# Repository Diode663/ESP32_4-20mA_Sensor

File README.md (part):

# ESP32 4-20mA ESPHome Sensor Board

Single-channel industrial 4-20mA current-loop reader, USB-C powered, built for ESPHome.

## Rev H (2026-11-11)

Rev G was never ordered; its files, fab package included, are at tag `rev-g`.
Rev H carries the changes that came out of an independent review of it
(`docs/Design_Review_2026-11-11_independent.md`). The sections further down
still describe Rev G except where they say Rev H.

| Change | Why |
|---|---|
| **mA input: D5 SMAJ12A -> SMAJ28A, new F1 (100 mA / 60 V PPTC) in series, new D6 (1N4007W) across the shunt.** Nets: `LOOP_IN` terminal side, `LOOP_RTN` shunt side | D5 did not conduct until 13 V with the 3.32 ohm shunt in parallel: a 0.5 kV surge put 5 A / 91 W peak through an 0805, and 24 V wired to the mA pin put 7 A through it. Now the shunt sees D6's ~1 V and F1 opens (`sim/8_input_protection.py`). Cost: D6 steals 1 ppm of the reading at 25 C, 77 ppm at 85 C |
| **R15 is a pull-down** | the loop supply stays off through reset, flashing and a hung firmware; ESPHome turns it on at boot. The same firmware runs on Rev G |
| **Silkscreen legend**: J2 pinout (top, and on the bottom under each pin), RESET, BOOT, board name and revision | Rev G carried designators only |
| **Routing by this board's own grid router** (`gridroute.py`), module supply scripted through C3 | 9 signal vias and 25 mm of track on the ground layer; Rev G's Freerouting result had 7 vias and 59 mm, with pin 2 fed through two vias |
| **Terminal corner re-laid**: F1 where D3 was, D6 beside it, D3 upright at the row's east end, D4 in the strip right of the terminal, TP1 beside R20, third fiducial moved to the west edge | to fit two more parts; nothing live is within 2.6 mm of the corner mounting hole's centre |
| **Schematic redrawn on A3**: every block wired (no connection made by label inside a block), functional symbols for J1, D1, U3, U4, U5 | Rev G's A2 sheet printed at half size and joined 20 connections by name |

DRC: the same nine library-footprint items as Rev G, nothing unconnected,
schematic parity clean. Not built or measured.

## Rev G at a glance (2026-09-20)

Rev G is the result of a second, independent design review
(`docs/Design_Review_2026-09-20_second_pass.md`). Every circuit change below
was simulated first; the decks are in `sim/` and run on KiCad's own bundled
ngspice.

| Change | Why |
|---|---|
| Limiter is now **constant-current**: R19 removed, R16 18 ohm, Q1 -> BCP53-16 (SOT-223) | Rev F's foldback could park a transmitter at ~9 V / 14 mA after a short or a hot-plug and report that as the reading |
| **D4** (1N4148W) in series after Q1 | a surge on `LOOP_V` drove Q1 backwards into the 24 V rail from ~25 V, long before the TVS conducted |
| **D3 -> SMAJ28A to GND**, new **D5** SMAJ12A from `LOOP_RTN` to GND | one TVS across the pair handled only differential surges; common-mode went through the shunt into the INA226 |
| **Soft-start load switch** Q3/Q4/R21/R22/C12 ahead of the boost | VBUS saw ~27 uF at attach against USB's 10 uF limit; it now sees 1 uF, and `MT_EN` low truly disconnects the loop supply |
| **J2 is 3-pin**: GND, mA in, +24 V out | a 3-wire or self-powered (sourcing) transmitter could not be connected at all |
| **J2 is a one-piece push-in block**, KEFA KF250NH-5.0-3P (`C976567`) | no separate plug to order or lose; solid and ferruled wire pushes straight in, the orange button releases it or opens it for bare stranded wire |
| **U1 is the ESP32-S3-WROOM-1U-N4** (`C2980296`): U.FL connector, external antenna | antenna goes on the enclosure, not inside it. **The board is unchanged** - see below |
| L1 4.7 -> **22 uH** | a quarter of the ripple current at this light load |
| Boost and INA226 re-placed to their **datasheet layout figures** | switched-current loop 28 -> 19 mm^2 with C11's ground 3.8 mm from U5's (was 9.7); C8 1.5 mm from VS (was 8.0, on the wrong side of the chip) |
| Top M2 holes moved from the corners to y = 16.8 mm | they were level with the antenna, 9.6 mm from the module |
| `pcblib`: swaps changed footprints, DRC runs with `--schematic-parity` | the board had kept 1.5 mm test pads the schematic dropped for 1.0 mm, and nothing could see it |

**State:** 28 nets / 35 no-connects match the specification exactly, ERC 0
errors, schematic parity clean, placement DRC 4 (all deliberate silk-at-edge)
+ 5 library-internal, 52 parts + 4 holes + 3 fiducials, BOM 34 lines / 47
placements. **Placed and routed** - 0 unconnected, DRC unchanged at 4 + 5; see
[Routing](#routing).

**Firmware:** `firmware/` holds the ESPHome configuration, and both of the
things this board's firmware had to do are done there:

1. A reading is published as *unknown*, not as a plausible number, whenever
   the loop is not trustworthy - including `LOOP_V` below 20 V with current
   flowing. On a sustained short (`LOOP_V` < 3 V) it drops `MT_EN`, which now
   removes the supply entirely, retries three times and then latches off.
2. Two-point calibration at 4 mA and 20 mA, captured from Home Assistant with
   a reference source and stored in flash. R12's 1 % tolerance and 200 ppm/°C
   drift and R20's fixed gain error all come out together; one point cannot
   remove them.

The firmware is a reusable ESPHome package, pulled by URL, so another board
built from this design tracks the same definition.

It also classifies faults to NAMUR NE43 and detects a backwards-wired sourcing
transmitter, which reads as negative current through the shunt. Validated on
ESPHome 2026.9.0: config clean, and it compiles to 47 % of the N4's
application partition. See `firmware/README.md`.

### Going back to the PCB-antenna module

The -1U was swapped in **without touching the board**, deliberately. Espressif's
datasheet gives the -1 and the -1U one land pattern (Figures 10 and 11 carry
identical dimensions; the -1 only adds the antenna area), so the new footprint
`WIFIM-SMD_ESP32-S3-WROOM-1U` copies the old one's 61 pads and its origin
unchanged and differs only in body outline and 3D model. The outline, the
6.5 mm the antenna would overhang, the keep-clear at the top edge and the
lowered top mounting holes are all still laid out for the -1.

To revert, change one line in `generate_schematic.py` (the old line is kept
there as a comment) and re-run both generators. No copper moves.

With the -1U fitted the radio has **no antenna of its own**: the U.FL pigtail
and antenna in `bom/non-bom-items.csv` are required, and the connector is
U.FL / IPEX generation 1 - the smaller Gen 3/4 (MHF3/MHF4) plugs do not mate.

## Calibration

**Do this before you trust a reading.** R12 is a 1 % shunt with 200 ppm/°C
drift, and R20 adds a fixed 1.19 % gain error to the voltage reading. A single
point cannot remove both a gain and an offset error, which is why there are
two. The firmware ships with the identity calibration, so an uncalibrated
board is out by whatever its own components happen to be.

You need a loop calibrator, or any adjustable current source you trust to
better than the accuracy you want out of the board.

1. Wire the calibrator into **J2 pins 3 and 2** as if it were a 2-wire
   transmitter — the board supplies the 24 V and the calibrator sinks the
   current. An active source works too: push into pin 2, return on pin 1, and
   turn *Loop power* off first so the two supplies do not fight.
2. Set **4.000 mA**. Watch the `Loop current (raw)` entity and wait for it to
   settle — the median filter takes about 3 s, so give it ten.
3. Press **Calibrate: capture 4 mA**.
4. Set **20.000 mA**, wait again, press **Calibrate: capture 20 mA**.
5. Read the **Calibration** entity. It reports the pair you captured together
   with the resulting gain and offset, for example
   `4mA=4.0123  20mA=19.9871  gain=1.00212  offset=-0.0208 mA`.
   A gain more than a couple of percent from 1.000 means something is wrong —
   check the shunt and the wiring rather than accepting it.

A capture is **refused** if the raw reading is more than 2 mA away from the
reference it claims to be, and the log says so. That is deliberate: it stops a
mistimed press silently destroying the calibration.

The result is written to flash and survives reboots and OTA updates.
**Calibrate: reset to factory** puts back the values compiled into the YAML.

Recalibrate if the board's ambient temperature changes substantially: the
shunt's 200 ppm/°C over a 40 °C swing is 0.8 % of reading, about 0.13 mA
across the span. Full procedure and the entity list are in
[`firmware/README.md`](firmware/README.md).

## Project files

```
esp32-4to20ma-board.kicad_pro     Project file
esp32-4to20ma-board.kicad_sch     The schematic — one A3 sheet in Rev H, A2 in Rev G (generated)
schematic.pdf                     PDF of the schematic
esp32-4to20ma-board.kicad_pcb     Board, 40x61mm portrait — placed and routed
setup_fab.py                      Stackup, netclasses, board rules, .kicad_dru (run before routing)
route_board.py                    Routes the board: scripted critical nets + replayed autoroute + pours
routelib.py                       Routing library (from the kicad-pcb-placement skill): drawing, the
                                  Freerouting hand-off, replay, DRC and pour reports
routing/autoroute.json            Freerouting's result (Rev G), replayed with --freerouting
gridroute.py                      Rev H: this board's own grid router (route_board.py --gridroute)
routing/gridroute.json            Its result, replayed by route_board.py by default
routing/drc.json                  The last full DRC report
build_package.py                  Builds fab/: gerbers zip, BOM, CPL, order notes (DRC-gated)
jlc_cpl.py, jlc_rotations.json    CPL exporter and this board's sourced rotation corrections
jlc_compare.py                    Derives those corrections from JLCPCB's own footprints
fab/                              The JLCPCB upload, regenerated by build_package.py
place_components.py               Places every part; the source of truth for the layout
pcblib.py                         PCB builder (from the kicad-pcb-placement skill)
.pcbgen-backup/                   Backups of the board and of the original footprints
sym-lib-table / fp-lib-table      Project-local + KiCad-standard library references
libraries/                        Project-local symbols, footprints, 3D models from LCSC
datasheets/manifest.json          Which manufacturer datasheet was read for each
                                  IC, and where to get it — the PDFs themselves
                                  are copyrighted and not in this repository
firmware/                         ESPHome configuration — a shared package plus
                                  a thin per-device file. See firmware/README.md
bom/bom.csv                       BOM with LCSC part numbers, for JLCPCB turnkey
bom/non-bom-items.csv             Parts to order that aren't on the board
bom_report.py                     Regenerates bom/bom.csv from the schematic
docs/Design_Review_2026-09-20.md  Design review (schematic + placement, pre-fab)
docs/Design_Review_2026-09-20_second_pass.md   Second, independent review - what Rev G fixes
sim/                              ngspice decks for the limiter, surge path and USB inrush
analysis/                         Analyzer JSON per run, tracked by manifest.json
generate_schematic.py             Generates the schematic — the source of truth
schlib.py                         Schematic builder (from the kicad-schematic-layout skill)
.schgen-backup/                   Automatic backups of any sheet the generator overwrote
verify_schematic.py               Diffs KiCad's extracted netlist against the spec
netlist_report.py                 Regenerates netlist_report.txt
netlist_report.txt                Pin-level connectivity listing for rework
erc_report.txt                    Verification output (0 errors)
render/pcb_top.png                3D top view, written by place_components.py
render/pcb_angled.png             3D angled view
render/pcb_bottom.png             3D bottom view
render/copper_top.svg, copper_bottom.svg   The copper layers as drawn
render/pcb.svg                    Vector top view
render/pcb_top_pad_overlay.png    The top view with the real pad rectangles drawn
                                  over it — how the J2 pitch error and the three
                                  misplaced 3D models were caught
```

## Schematic organisation

The schematic is **one A2 sheet**. At 47 parts plus five test points the design still isn't complex
enough to justify hierarchy, which would only add page-flipping. The sheet has
four sections, tiled in signal-flow order:

```
USB-C INPUT & ESD   ->   3.3 V REGULATOR & LED   ->   ESP32-S3 MODULE
24 V BOOST CONVERTER   ->   LOOP CURRENT LIMITER   ->   LOOP TERMINAL & MEASUREMENT
TEST POINTS, sheet notes
```

One block per **circuit**, seven in all (it was twelve). The boost converter is
one block with its load switch, input and output in it, not three; the module is
one block with its reset, boot, pull-ups, decoupling and strapping notes, not
"module" and "support circuitry". Reference sheets for these parts are drawn the
same way - Adafruit's ESP32-S3 Feather divides its sheet into "POWER AND
FILTERING", "USB TO SERIAL CONVERTER", "LIPO CHARGING" and so on, with the module
and everything that serves it in one region.

Drawing conventions throughout:

- **Flow and orientation:** signals flow left to right; supplies come in from
  the top and grounds leave at the bottom.
- **Power rails:** `GND`, `+3V3`, `+5V` and `+24V` are drawn as power-port
  symbols, not text labels.
- **Links between sections:** the sections connect by net label — `USB_P` and
  `USB_N` from USB-C to the ESP32-S3, and `I2C_SDA` and `I2C_SCL` from the
  ESP32-S3 to the INA226.
- **Wires vs labels:** components are wired with real wires and junctions.
  Short labelled stubs are used only where a wire would cross another net: the
  USB-C flip pairing, the CC pulldowns, the MT3608's FB/SW pins and the INA226
  sense lines. There are no wire crossings on the sheet.
- **Blocks and notes:** each circuit is drawn inside `s.block_start(title)` /
  `s.block_end()`, with its design calculations as notes *inside* the block.
  No rectangle is typed by hand: `schlib` derives each outline from what is in
  the block (parts, field text, labels, notes, measured at KiCad's own glyph
  widths) plus 5 mm, and `arrange()` flows the blocks across the page in the
  order they are declared. `check_text()` then reads KiCad's render and fails
  on any string or part body within 0.8 mm of an outline. Run against the old
  hand-boxed sheet that check reports about a hundred such faults (`I2C_SCL`
  on the module box's edge, the strapping notes across another, `+24V` on the
  limiter's top line); on this sheet, none.

### Regenerating

`generate_schematic.py` is the source of truth. Edit it rather than the
`.kicad_sch` file, which gets regenerated:

```bash
python3 generate_schematic.py && python3 netlist_report.py
```

The generator re-checks the geometry and verifies the drawn netlist against its
`NETS` spec, using KiCad's own netlister. It also runs ERC, then a text check.
The text check reads KiCad's rendered SVG and flags any reference, value,
label or note that is drawn sideways, lies on a wire, or overlaps a part.

If the sheet was changed in KiCad since the last run, the generator refuses to
overwrite it. It backs the file up to `.schgen-backup/` first; port your edits
into the script, then rerun with `--force`.

### PCB after the switch to one sheet

Footprints are linked to schematic symbols by the symbols' sheet path, and
flattening the hierarchy changed every path. Update the PCB like this:

1. Run **Tools → Update PCB from Schematic**.
2. Tick **"Re-link footprints to schematic symbols based on their reference
   designators"**. All references are unchanged, so every footprint re-links.
3. Expect local net names to change prefix, e.g. `/USB-C Input…/CC1` → `/CC1`.
   The board has almost no routing yet, so nothing is lost.

From now on, UUIDs are deterministic, so regenerating won't break the links
again.

## Routing

The board is **routed**: 0 unconnected items, DRC at the same 4 + 5 it had as a
bare placement (four deliberate silk-at-edge warnings, five inside library
footprints), schematic parity clean. Two scripts, run in this order after
`place_components.py`:

```bash
"C:\Program Files\KiCad\10.0\bin\python.exe" setup_fab.py
"C:\Program Files\KiCad\10.0\bin\python.exe" route_board.py
```

`setup_fab.py` writes the JLCPCB 2-layer stackup (JLC0216A, 1.6 mm), the
netclasses (`USB` 0.25/0.20 mm pair, `POWER` 0.4 mm, `LOOP` 0.3 mm with 0.25 mm
clearance, `GND`) and a three-rule `.kicad_dru`. The board constraints are the
ones in *Fabrication rules* below, unchanged.

`route_board.py` is a **hybrid**. It removes every track, via and copper zone
and redraws them, so it is safe to run again after any placement change - and
it **discards hand edits to tracks**; change the script, or stop using it.

| Scripted (255 segments and vias) | Why it is not left to an autorouter |
|---|---|
| MT3608 boost | Figure 3: CIN returns to pin 2 *under* the IC, COUT returns down the east side of D2, the switch node is two stubs under 2 mm, FB is 1 mm from pin 3 to the divider |
| INA226 taps | Figure 30: the two taps enter the shunt pads on their inner faces as a pair; load current enters and leaves on the outer faces. R14.1 is on GND by name only, so the pour is kept off it - it sees the shunt pad and nothing else |
| USB-C fan-out, D1, the pair | see below |
| +5V, +3V3 and +24V trunks, the 24 V loop | widths, and the one place each may change layer |
| Q1's copper | tab and pin 2 are one area top and bottom (40 + 45 mm2), six vias under the body |
| every ground via, both pours | the bottom pour is **one unbroken piece** of 2179 mm2 |

Freerouting 2.4.1 does the rest - EN, IO0, MT_EN, I2C, the load-switch gate
network, the LED and the +3V3 branches: 113 segments, 7 vias. It runs only with
`route_board.py --autoroute`; its result is stored in `routing/autoroute.json`
and replayed on every ordinary run, so the board is reproducible (two runs give
byte-identical tracks) without Java and without re-rolling the autorouter. Run
`--autoroute` again if a part that only it touches moves. Runs differ: each one is
judged by KiCad's own DRC on a trial board and repeated (up to three times) until
nothing is left open, and `FREEROUTING_BEST_OF=3` keeps the best of three. Look at
the result either way - one re-roll here passed DRC with the bottom ground in two
pieces. It expects
`~/tools/freerouting/` (or `FREEROUTING_HOME`) to hold `freerouting-2.4.1.jar` and a Java
25 runtime; it runs headless, with the fan-out stage and telemetry off.

Three things about KiCad 10 + Freerouting 2.4.1 that cost time and are handled
in `routelib.py`: KiCad exports existing tracks as `(type route)`, which an
autorouter may rip up, so the DSN is patched to `(type protect)`; KiCad's
`ImportSpecctraSES` then refuses the session file, so the script reads the SES
itself and takes only unprotected items on nets it did not route; and
Freerouting does not count a track that ends inside a pad, off its centre, as
connected, so whatever it adds to a fully scripted net is dropped as a duplicate.

**USB.** J1's D+/D- pads read N P N P. The *outer* two (B7, B6) are the main
path - D- west, D+ east - which is the order both D1 (turned 180 degrees) and
module pins 13/14 want, so the pair never crosses itself. A6 joins D+ on the top
layer; A7 joins D- by the only bottom strap in the pair, 2.9 mm. The two VBUS
pins are joined on the board by a 4.8 mm bottom link under D1, which also feeds
D1's pin 5 (a receptacle's VBUS pins are only joined inside a plug). The pair
is 39.6 / 43.8 mm including those stubs; at the S3's 12 Mbit/s full speed the
4 mm difference is about 25 ps against an 83 ns bit.

**Where the bottom ground is cut**, all of it: the two USB-entry links above,
one SDA hop of 9.8 mm that passes under the pair at 45 degrees, +3V3 to the
pull-ups and U3 (39 mm in two runs, about 1 mA), and LOOP_V's sense tap to R20
(10.5 mm). Nothing crosses under the boost converter.

**Placement changes routing asked for** (all in `place_components.py`): D1
turned 180 degrees and moved up 1.5 mm; R7 and R8 moved into the lanes between
VBUS and the pair, 2 mm from their pins; R10/R11 moved beside U5, which lets
+24V reach the limiter on the top layer; C9 up 0.1 mm; R6 and R15 swapped so
each pull-up sits under its own pin (before that, MT_EN took a 25 mm detour
under the module).

Still open after routing: nothing has been measured. EMC and Q1's temperature
are as designed, not as tested.

## Fabrication package (JLCPCB)

```bash
"C:\Program Files\KiCad\10.0\bin\python.exe" build_package.py
```

writes `fab/`: `esp32-4to20ma-board_gerbers.zip` (9 layers + separate PTH and NPTH drill
files + drill maps), `_bom.csv` (34 lines, 47 parts), `_cpl.csv` (47 placements) and
`ORDER_NOTES.txt`. It refuses to build unless DRC is clean apart from the two accepted
errors inside J1's library footprint, the BOM is read from the board so it is exactly
what is placed, and the build stops if BOM and CPL designators differ or the board
disagrees with `bom/bom.csv`.

Three things to know before ordering:

- **Standard PCBA, not Economic.** JLCPCB lists the ESP32-S3-WROOM-1U-N4 (`C2980296`)
  as "PCBA Type: Standard Only". J2 is the one through-hole part; it is "Economic and
  Standard", wave-soldered, and rides along.
- **Rotations were derived, not guessed.** `jlc_compare.py` fetches JLCPCB's own
  footprint for each part's LCSC number and matches it to the board's, pad number to
  pad number. Every project-library footprint is already at JLCPCB's zero with zero
  origin offset. Only the four stock-KiCad transistor footprints differ - Q1 (SOT-223)
  and Q2, Q3, Q4 (SOT-23) need +180 - and those are in `jlc_rotations.json`, each with
  its evidence. None of it has been seen in JLCPCB's placement preview yet:
  `ORDER_NOTES.txt` says what each part should look like there. LED1's polarity rests on
  pad 1 being the cathode in their footprint (its silk says so; their symbol could not
  be fetched to confirm) - a reversed LED only stays dark.
- **All 34 lines were in stock at LCSC on 2026-09-20**, thinnest: U1 1,702, J2 1,990,
  R12 4,810, C10/C11 8,605. Nine manufacturer names in the BOM were wrong (the Samsung
  capacitors were listed as CCTC, the FOJAN resistors as Uniroyal, LED1 as
  "Nichia-compatible" - it is Nationstar) and were corrected in `generate_schematic.py`;
  every MPN and LCSC number was already right.

## PCB placement

Components are placed on a **40 × 61 mm** two-layer board,
portrait, with 1 mm rounded corners, by `place_components.py` on top of
`pcblib.py`. Run it with KiCad's Python:

```bash
"C:\Program Files\KiCad\10.0\bin\python.exe" place_components.py
```

**Re-running resets every part to the table.** Once you start adjusting
placement by hand, editing the `PLACEMENT` table is the only safe way to
change it. `pcblib` enforces this: it hashes the board each time it writes,
and if the file has changed since, it backs it up to `.pcbgen-backup/` and
refuses. Port your changes into the table, then run with `--force`.

Each run also:

- imports any footprint the schematic has and the board lacks, and reloads
  every footprint from its library, so schematic and `.kicad_mod` changes
  both reach the board without a trip through the KiCad GUI;
- re-links every footprint to its schematic symbol by UUID and assigns pad
  nets from KiCad's own netlist, so the ratsnest is right immediately and
  *Update PCB from Schematic* finds nothing to change;
- puts each reference designator where it clears pads, silkscreen, its
  neighbours and the board edge, at 0.15 mm stroke (JLCPCB's minimum);
- checks courtyard overlaps, **pad-to-pad gaps between different parts**,
  off-board parts and keep-out intrusions before saving, and aborts rather
  than writing a broken board. The pad-gap check matters: 8 of these 52
  footprints draw their courtyard around the body and leave the pads
  outside it (SW1 by 2.66 mm), so courtyard clearance flatters them. It
  caught the buttons sitting 0.35 mm from the module's pad row and the CC
  resistors 0.21 mm from J1 — both legal for DRC, both far too tight;
- runs DRC and **splits it in two** — placement problems, which are yours to
  fix, and problems inside a single library footprint, which moving parts
  cannot fix. Expect **4** and **5** respectively, 0 unconnected items, and
  `schematic parity: clean`. (Run it after moving a part and it will report
  shorts until `route_board.py` has been run again - the old tracks are still
  where the part used to be);
- prints the span of the critical nets, so the claims below are measurable
  rather than asserted;
- writes `render/pcb_top.png`, `render/pcb_angled.png` and `render/pcb.svg`.

All 5 placement-level warnings are `silk_edge_clearance`, on J1 where the
USB-C shell meets the board edge and on U1 where the module crosses the top
edge to overhang it - both deliberate.

`tidy_references` orders parts by `_part_extent()` (pads, silkscreen and
courtyard, deliberately blind to the text) with a natural sort on the
reference as tie-break, so repeated runs give byte-identical designator
positions. In Rev G it also searches further: the same eight spots with the
text turned upright, then both again up to 2 mm out, and it treats other
parts' courtyards as obstacles - pads and silk alone left the middle of the
SOT-223 looking like free board, and it put R12's designator there.

That still cannot solve the lower-right corner, which holds the limiter, the
sense network, two TVS diodes and the terminal. `REF_PINS` in
`place_components.py` places 18 designators by hand, each checked against DRC.

Five test points (`TP1`-`TP5`, 1.0 mm bare pads) sit on `LOOP_V`, `LOOP_RTN`
(`LOOP_IN` in Rev H), `+24V`, `+3V3` and `MT_EN`. In Rev H TP1 is the bare pad
beside R20 and carries no designator: there is no room for one. They are real schematic symbols - that is the only
way they get a net - but carry `in_bom=False`. Until Rev G the *board* still
held 1.5 mm pads: `pcblib` never propagated a footprint changed in the
schematic. It does now, and `Board.drc()` runs with `--schematic-parity`.

Four M2 holes: the bottom pair 3.5 mm in from the corners beside the
connectors, the top pair at y = 16.8 mm beside the buttons - 19 mm from the
antenna (Espressif asks for ~15 mm clear of metal) and 1.8 mm clear of the
button pads for a 4.6 mm standoff.

Three fiducials (`FID1`/`FID2`/`FID3`, 1 mm copper in a 2 mm mask opening)
sit at (4, 7), (36, 7) and (36, 54) mm — an L, 4 mm in from the edges, which
clears JLCPCB's 3.85 mm minimum. They are board-only footprints: no schematic
symbol, excluded from the BOM and from the placement file, so they cannot
become orphan designators in a PCBA upload.

`pcblib.py` is the shared library from the `kicad-pcb-placement` skill; it is
copied in so the project stays self-contained.

### Why the board is this shape

**Portrait, 40 × 61 mm.** About the minimum for this part set. The
measured extents are 2.40 mm of margin left and right — set by the M2
mounting holes, not by any component — J1's shell flush with the bottom edge,
and C3 1.80 mm from the top. Width is pinned by the bottom edge: J2's
courtyard is 12 mm wide (it includes the mating plug), J1's is about 10, and
the two corner mounting holes take 6 mm between them. Height is pinned by the
vertical stack: module 19 mm, buttons 7, boost 14, sense chain 10, connectors
10. The extra 1 mm over the first attempt buys ~1 mm of clearance either side
of the buttons.

**The antenna overhangs the top edge.** The board stops level with the start
of the module's pad rows, so 6.5 mm of antenna hangs in free air —
Espressif's best case, and better than any keep-out on a populated board. The
module is then soldered on three edges with that 6.5 mm unsupported, so the
enclosure needs clearance around it and must not press on it. There is no
antenna keep-out zone any more: the overhang replaced it. At routing time,
keep the ground pour back from the top edge.

**Both connectors are on the bottom edge**, as asked. Note that J2 is a
*vertical* plug-in header — the mating plug drops in from above — so its
position at the edge is for cable dressing, not because it needs edge access.

| Area | What's there | Why |
|---|---|---|
| Top, antenna overhanging | ESP32-S3 module, centred | No PCB under the antenna at all |
| Upper left | C3 at pin 2 (3V3), R1/C1 at EN, C2 bulk, R5 at pin 12 | The module's 3V3, EN and SDA pins are all on the left flank; each part sits level with the pin it serves |
| Below the module | RESET and BOOT buttons, R6 and R15 in the gap between them | SCL (17) and the loop enable IO10 (18) come out of the module's bottom edge, right where their pull-ups sit |
| Left, middle | AP2112K LDO + C6/C7 | Between its 5 V source at the bottom and its 3.3 V loads above |
| Right, middle | MT3608 boost: C10, L1, U5, D2, C11 in one tight loop, FB divider by the FB pin | Per the MT3608 datasheet, and the furthest point on the board from the antenna |
| Right, lower | INA226, shunt R12, R13/R14 tapping its two ends, C9 | Kelvin sense per the INA226 datasheet; U3 faces the shunt with its inputs and the MCU with its I²C |
| Bottom left | USB-C, D1 ESD clamp directly above it, CC pulldowns either side, LED on the left edge | D+/D− run connector → clamp → module with nothing in the way |
| Bottom right | 4-20 mA terminal J2, TVS D3 just above it aligned with its pins | Field wiring lands at the edge and is clamped immediately |

Measured after placement:

| Net | Span | Comment |
|---|---|---|
| `/MT_SW` | 5.45 mm | the boost switching node — the one that matters |
| `/LOOP_RTN` | 9.68 mm | terminal to shunt |
| Kelvin taps | 1.69 mm | R13 and R14 each sit against the shunt pad they measure |
| `/USB_P` / `/USB_N` | 35–36 mm | the cost of portrait: connector at the bottom, module at the top. Fine for the S3's 12 Mbps full-speed USB, but route them as a pair over unbroken ground |
| `/I2C_SDA` / `/I2C_SCL` | 28–35 mm | 400 kHz, length is irrelevant |

### Loop short-circuit protection

A boost converter cannot disconnect its output: `Vin -> L1 -> D2 -> Vout` is a
DC path that conducts with U5 disabled. Shorting Loop+ to Loop- therefore fed
~1.35 A from the 5 V rail straight through the shunt, destroying R12 (about
6 W in an 0805) and browning out the board.

The fix is a series element, which costs only compliance voltage, never
accuracy, because the transmitter regulates the loop current:

| | |
|---|---|
| Q1 | PNP pass element, **BCP53-16 in SOT-223** (80 V, 1.5 W) |
| R16 | 18 ohm sense; Q2 steals Q1's base drive once the drop across it reaches a Vbe |
| R18 | 1 k in Q2's base - limits its base current, nothing more |
| R17 | 47 k base bias, ~0.5 mA; BCP53-16 hFE >= 100 turns that into 50 mA |
| D4 | 1N4148W in series after Q1: blocks `LOOP_V` from driving Q1 backwards |

`Ilim = Vbe(Q2) / R16`: **35 / 33 / 30 / 27 mA at -20 / 25 / 60 / 85 C**
(`sim/6_rev_g_limiter.py`), so a 24 mA over-range reads at any temperature.
R16 + Q1 + D4 cost 1.2 V: **22.8 V at J2 with 20 mA flowing**.

**It is deliberately not a foldback limiter, and Rev F's was a mistake.** A
2-wire transmitter is a constant-current load: it draws the same current at
any voltage above its lift-off, so its load line can cross a foldback curve
twice, and the lower crossing is stable. After a short was cleared, or a
transmitter was plugged into a live J2, Rev F could sit at ~9 V / 14 mA
indefinitely with the process at 20 mA - and report 14 mA
(`sim/recover.py`). Its short-circuit current was also the small difference of
two ~0.6 V terms and fell to zero by ~65 C. Cold power-up happened to work,
which is why it looked fine.

The price is dissipation: a dead short puts the whole rail across Q1,
24 V x 35 mA = **0.85 W**. That is what the SOT-223 is for - pour `LOOP_C`
generously around the tab and stitch it to the bottom layer. Firmware should
also drop `MT_EN` on a sustained short; with the Rev G load switch that
removes the supply entirely rather than leaving 4.6 V behind.

### Field protection

**Rev H** keeps D3 and replaces the mA wire's single clamp with three parts:
D5 (now SMAJ28A, so 24 V on that pin is inside its stand-off) at the terminal,
F1 (100 mA hold, 60 V PPTC) in series, and D6 (1N4007W) across the shunt. A
surge or a mis-wired 24 V supply then puts D6's forward drop across the shunt
- 0.3 to 1 W peak for microseconds, or until F1 opens - where Rev G put
91 W or 7 A (`sim/8_input_protection.py`). The rest of this section is Rev G.

Each field wire has its own TVS **to ground**, within 6 mm of its terminal
pin: D3 (SMAJ28A, clamps at 45 V) on `LOOP_V`, D5 (SMAJ12A, clamps under
20 V) on `LOOP_RTN`. Rev F had one SMAJ36A *across* the pair, which did
nothing for a common-mode surge: that returned through R12, and the INA226's
inputs saw `I x 3.32 ohm` through only 10 ohm. D5 sits at 80 mV in normal
operation and leaks nanoamps, so it costs no accuracy; and D3's leakage no
longer flows through the shunt.

D4 matters as much as the TVS. `LOOP_V` was Q1's collector, and a PNP's
collector-base junction is a diode: from ~25 V it conducted backwards, the
emitter-base junction avalanched at ~7 V of reverse bias, and the surge went
into the 24 V rail through R16 - toward U5's SW pin, rated 30 V absolute - all
before the old 36 V TVS reached breakdown (`sim/4_reverse_conduction.py`).
With D4 the reverse current is zero to beyond D3's clamp. It is a 1N4148W
rather than a Schottky because it sees the clamp minus the rail in reverse.

### Soft-start load switch

Q3 (AO3401A) sits between VBUS and everything the boost hangs on it: C10, and
C11 through L1/D2. Q4 (2N7002) turns it on from `MT_EN`; U5's own EN now rides
on its switched input. C12 is gate-to-**source** on purpose - a gate-to-drain
(Miller) capacitor was tried first and fails at hot-plug, because with the
drain at 0 V it drags the gate low as VBUS steps up and turns Q3 hard on for
the very edge it is meant to soften. Simulated (`sim/7_usb_inrush.py`): VBUS
sees **1.0 uF at attach, down from 26.8 uF** (USB allows 10), then a 0.33 A
peak 4 ms later as the boost input charges.

The INA226's VBUS tap moved to the **field side** of the limiter, so a short
shows up twice over: the current reads saturated (anything past 24.67 mA) and
the loop voltage collapses. Firmware can tell a shorted field pair from an
open one.

### J1's hole clearance, and why the rule moved

All four `hole_clearance` errors were inside J1's own footprint — its two
0.70 mm NPTH locating pegs against its own pads, nothing to do with placement.
JLCPCB publishes **0.20 mm** NPTH-to-track for 2-layer boards; this project was
running a stricter 0.25 mm, so half the errors existed only because of our own
rule. `min_hole_clearance` is now 0.20 mm and the count drops to two.

The two that remain (0.1812 mm, 0.019 mm inside JLCPCB's limit) are an
**accepted deviation**: they are on the *duplicated* GND pads — A1/B12 and
B1/A12 are the same nets on both sides of the receptacle — so a drill breakout
into one would not open the connection. If JLCPCB objects at DFM review, the
fallback is to trim those two pads by ~0.07 mm, which costs about 6 % of their
solder area and clears even the old rule.

### Fabrication rules (JLCPCB, 2-layer)

Board Setup now carries JLCPCB's published capabilities. Where the board was
already stricter it was left alone — being tighter than the fab is a design
choice, being looser is a defect:

| Rule | Was | Now | JLCPCB |
|---|---|---|---|
| Minimum clearance | **0.0 (off)** | 0.127 | 0.127 |
| Silkscreen line width (default) | 0.10 | 0.15 | 0.15 |
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
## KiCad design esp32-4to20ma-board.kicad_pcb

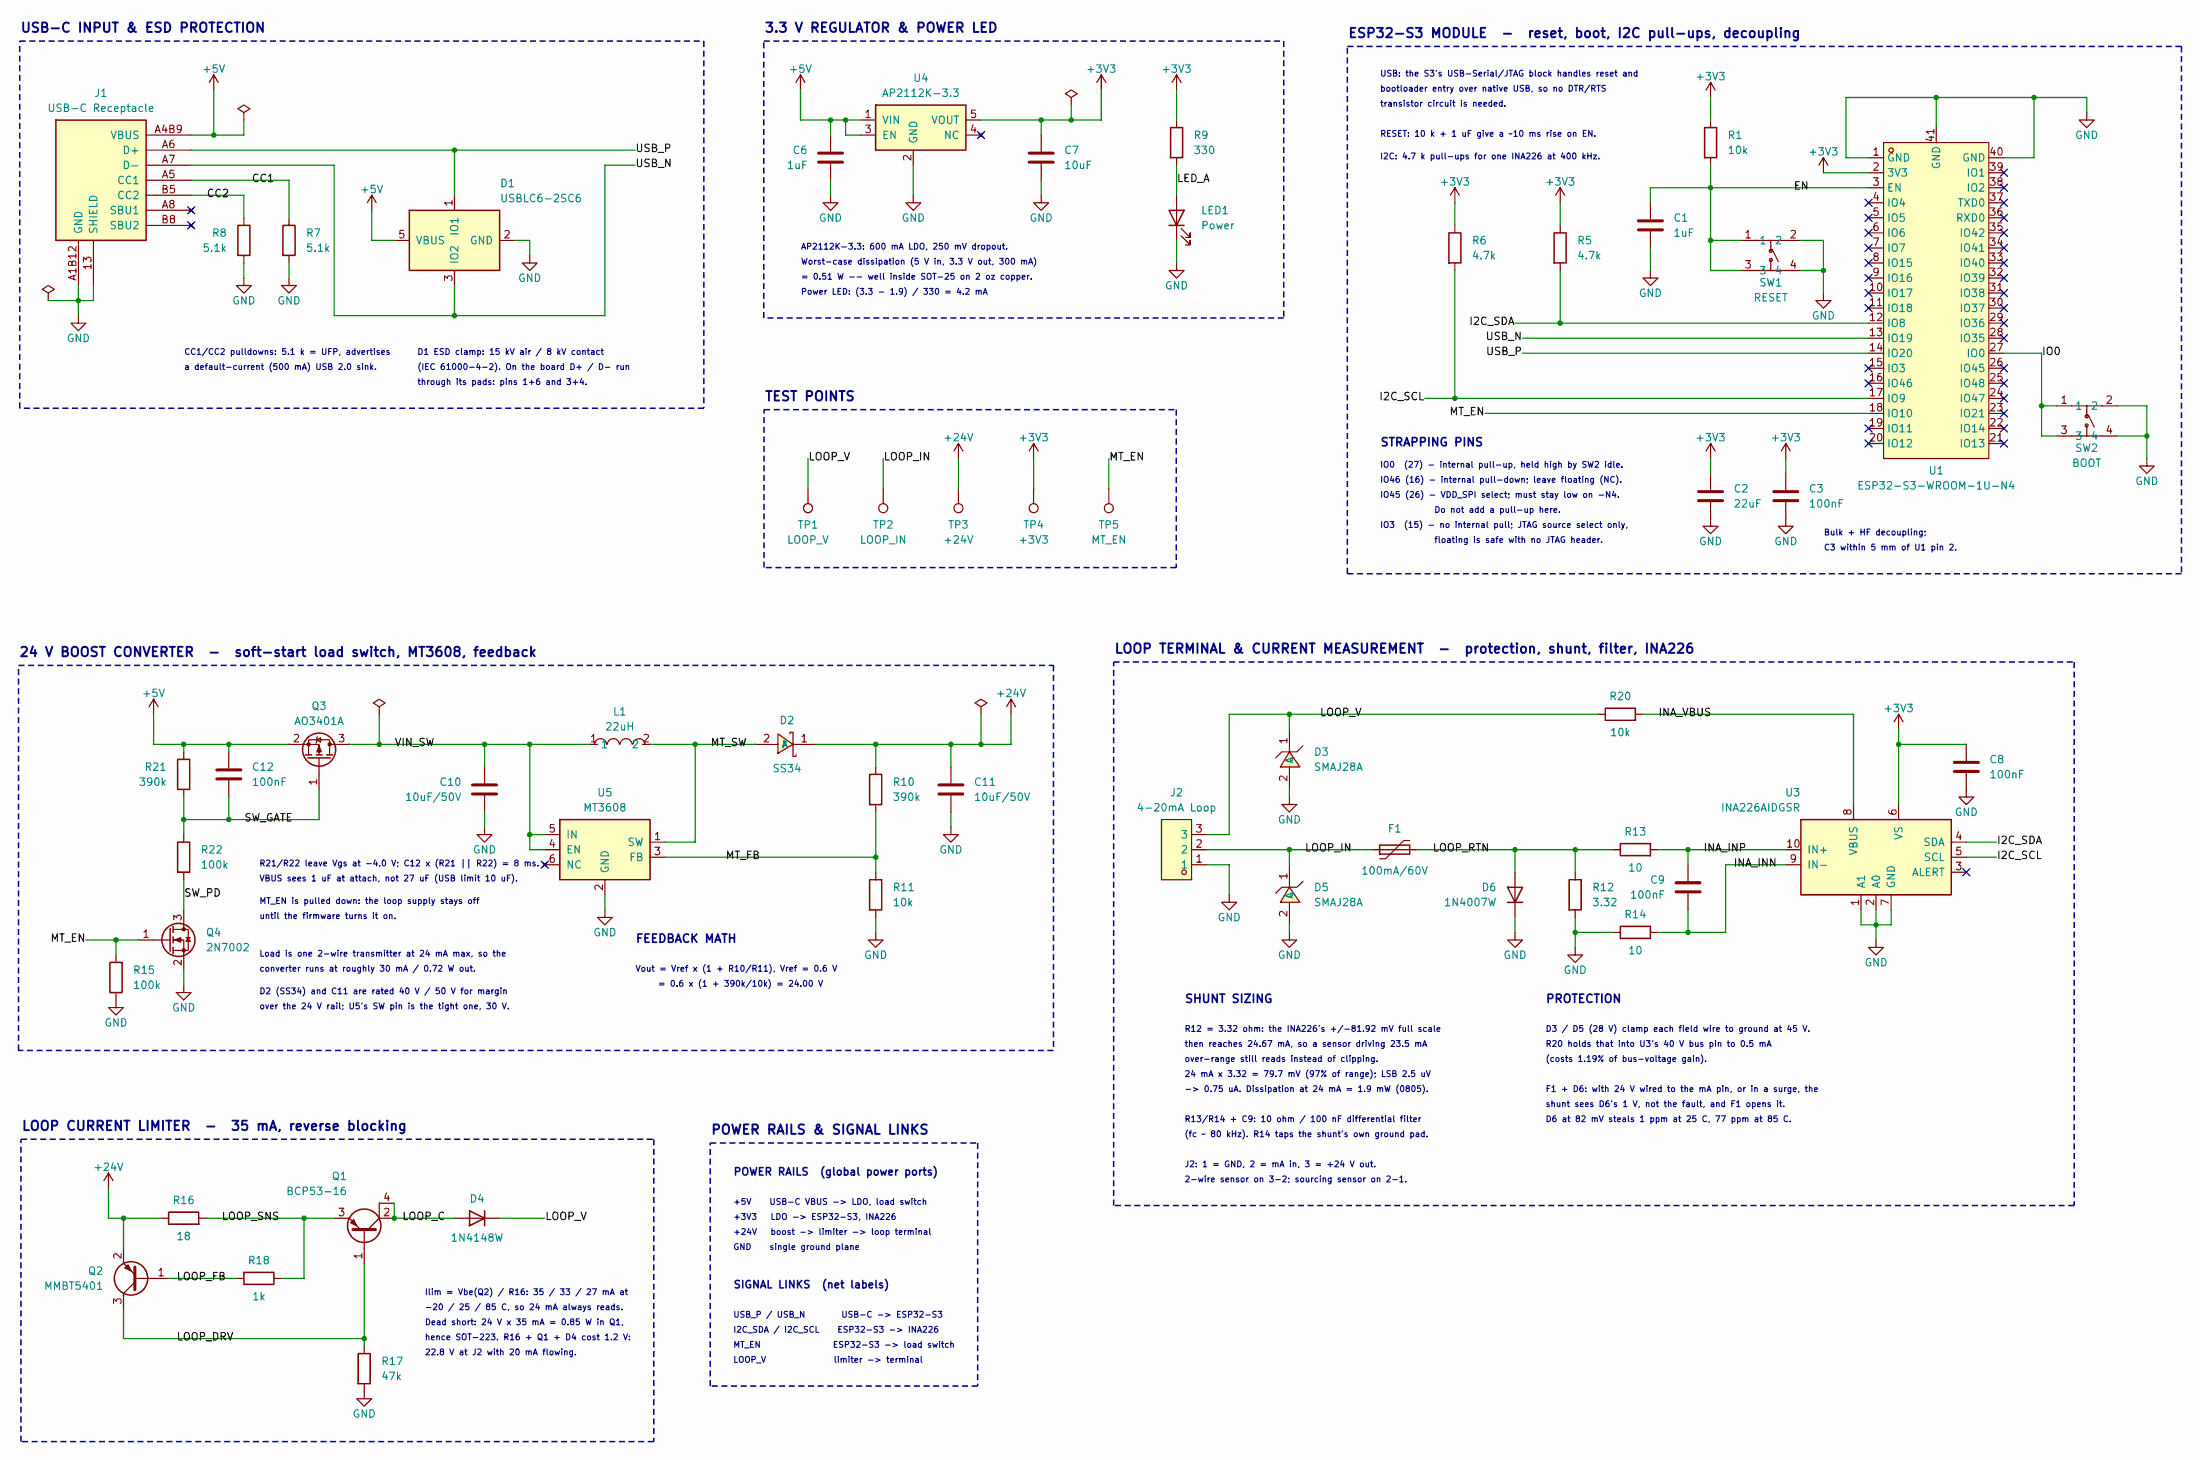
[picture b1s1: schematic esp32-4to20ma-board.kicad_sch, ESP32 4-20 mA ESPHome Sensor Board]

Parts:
C1, C6: 1uF; C_0402_1005Metric; MPN CL05A105KA5NQNC; LCSC C52923
C2: 22uF; C_0805_2012Metric; MPN CL21A226MAQNNNE; LCSC C45783
C3, C8, C9, C12: 100nF; C_0402_1005Metric; MPN CL05B104KO5NNNC; LCSC C1525
C7: 10uF; C_0603_1608Metric; MPN CL10A106KP8NNNC; LCSC C19702
C10, C11: 10uF/50V; C_1210_3225Metric; MPN CS3225X7R106K500NRL; LCSC C2918502
D1: USBLC6-2SC6; SOT-23-6_L2.9-W1.6-P0.95-LS2.8-BL; MPN USBLC6-2SC6; LCSC C2687116
D2: SS34; SMA_L4.3-W2.6-LS5.2-RD; MPN SS34; LCSC C8678
D3, D5: SMAJ28A; SMA_L4.3-W2.6-LS5.2-RD; MPN SMAJ28A; LCSC C353458
D4: 1N4148W; D_SOD-123; MPN 1N4148W; LCSC C81598
D6: 1N4007W; D_SOD-123F; MPN 1N4007W; LCSC C7528871
F1: 100mA/60V; Fuse_1206_3216Metric; MPN nSMD010; LCSC C70065
J1: USB-C Receptacle; USB-C-SMD_TYPE-C-16PIN-2MD-073; MPN TYPE-C 16PIN 2MD(073); LCSC C2765186
J2: 4-20mA Loop; CONN-TH_KF250NH-5.0-3P; MPN KF250NH-5.0-3P; LCSC C976567
L1: 22uH; IND-SMD_L4.0-W4.0_FNR40XXS; MPN FNR4030S220MT; LCSC C167883
LED1: Power; LED_0805_2012Metric; MPN NCD0805R1; LCSC C84256
Q1: BCP53-16; SOT-223; MPN BCP53-16; LCSC C148109
Q2: MMBT5401; SOT-23; MPN MMBT5401; LCSC C8326
Q3: AO3401A; SOT-23; MPN AO3401A; LCSC C15127
Q4: 2N7002; SOT-23; MPN 2N7002; LCSC C8545
R1, R11, R20: 10k; R_0402_1005Metric; MPN 0402WGF1002TCE; LCSC C25744
R5, R6: 4.7k; R_0402_1005Metric; MPN 0402WGF4701TCE; LCSC C25900
R7, R8: 5.1k; R_0402_1005Metric; MPN 0402WGF5101TCE; LCSC C25905
R9: 330; R_0402_1005Metric; MPN 0402WGF3300TCE; LCSC C25104
R10, R21: 390k; R_0402_1005Metric; MPN FRC0402F3903TS; LCSC C2909352
R12: 3.32; R_0805_2012Metric; MPN FRC0805F3R32TS; LCSC C3013220
R13, R14: 10; R_0402_1005Metric; MPN 0402WGF100JTCE; LCSC C25077
R15, R22: 100k; R_0402_1005Metric; MPN 0402WGF1003TCE; LCSC C25741
R16: 18; R_0402_1005Metric; MPN RC0402FR-0718RL; LCSC C138043
R17: 47k; R_0402_1005Metric; MPN 0402WGF4702TCE; LCSC C25792
R18: 1k; R_0402_1005Metric; MPN 0402WGF1001TCE; LCSC C11702
SW1: RESET; SW-SMD_4P-L6.0-W6.0-P4.50-LS9.0_H5.0; MPN KH-6X6X5H-STM; LCSC C2837531
SW2: BOOT; SW-SMD_4P-L6.0-W6.0-P4.50-LS9.0_H5.0; MPN KH-6X6X5H-STM; LCSC C2837531
TP1: LOOP_V; TestPoint_Pad_D1.0mm
TP2: LOOP_IN; TestPoint_Pad_D1.0mm
TP3: +24V; TestPoint_Pad_D1.0mm
TP4: +3V3; TestPoint_Pad_D1.0mm
TP5: MT_EN; TestPoint_Pad_D1.0mm
U1: ESP32-S3-WROOM-1U-N4; WIFIM-SMD_ESP32-S3-WROOM-1U; MPN ESP32-S3-WROOM-1U-N4; LCSC C2980296
U3: INA226AIDGSR; MSOP-10_L3.0-W3.0-P0.50-LS5.0-BL; MPN INA226AIDGSR; LCSC C49851
U4: AP2112K-3.3; SOT-25-5_L2.9-W1.6-P0.95-LS2.8-BL; MPN AP2112K-3.3TRG1; LCSC C51118
U5: MT3608; SOT-23-6_L2.9-W1.6-P0.95-LS2.8-BL; MPN MT3608; LCSC C84817

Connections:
/CC1: J1.A5 (CC1), R7.1
/CC2: J1.B5 (CC2), R8.1
/EN: C1.1, R1.2, SW1.1, SW1.3, U1.3 (EN)
/I2C_SCL: R6.2, U1.17 (IO9), U3.5 (SCL)
/I2C_SDA: R5.2, U1.12 (IO8), U3.4 (SDA)
/INA_INN: C9.2, R14.2, U3.9 (IN-)
/INA_INP: C9.1, R13.2, U3.10 (IN+)
/INA_VBUS: R20.2, U3.8 (VBUS)
/IO0: SW2.1, SW2.3, U1.27 (IO0)
/LED_A: LED1.2 (A), R9.2
/LOOP_C: D4.2 (A), Q1.2 (C), Q1.4 (C)
/LOOP_DRV: Q1.1 (B), Q2.3 (C), R17.1
/LOOP_FB: Q2.1 (B), R18.2
/LOOP_IN: D5.1 (C), F1.1, J2.2, TP2.1
/LOOP_RTN: D6.2 (A), F1.2, R12.1, R13.1
/LOOP_SNS: Q1.3 (E), R16.2, R18.1
/LOOP_V: D3.1 (C), D4.1 (K), J2.3, R20.1, TP1.1
/MT_EN: Q4.1 (G), R15.2, TP5.1, U1.18 (IO10)
/MT_FB: R10.2, R11.1, U5.3 (FB)
/MT_SW: D2.2 (A), L1.2, U5.1 (SW)
/SW_GATE: C12.2, Q3.1 (G), R21.2, R22.1
/SW_PD: Q4.3 (D), R22.2
/USB_N: D1.3 (IO2), D1.4 (IO2), J1.A7 (D-), J1.B7 (D-), U1.13 (IO19)
/USB_P: D1.1 (IO1), D1.6 (IO1), J1.A6 (D+), J1.B6 (D+), U1.14 (IO20)

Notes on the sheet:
IO45 (26) - VDD_SPI select; must stay low on -N4.
I2C_SDA / I2C_SCL ESP32-S3 -> INA226
AP2112K-3.3: 600 mA LDO, 250 mV dropout.
shunt sees D6's 1 V, not the fault, and F1 opens it.
J2: 1 = GND, 2 = mA in, 3 = +24 V out.
IO3 (15) - no internal pull; JTAG source select only,
IO46 (16) - internal pull-down; leave floating (NC).
R12 = 3.32 ohm: the INA226's +/-81.92 mV full scale
24 mA x 3.32 = 79.7 mV (97% of range); LSB 2.5 uV
3.3 V REGULATOR & POWER LED
over-range still reads instead of clipping.
I2C: 4.7 k pull-ups for one INA226 at 400 kHz.
Worst-case dissipation (5 V in, 3.3 V out, 300 mA)
SHUNT SIZING
+5V USB-C VBUS -> LDO, load switch
converter runs at roughly 30 mA / 0.72 W out.
R13/R14 + C9: 10 ohm / 100 nF differential filter
F1 + D6: with 24 V wired to the mA pin, or in a surge, the
2-wire sensor on 3-2; sourcing sensor on 2-1.
24 V BOOST CONVERTER - soft-start load switch, MT3608, feedback
then reaches 24.67 mA, so a sensor driving 23.5 mA
(costs 1.19% of bus-voltage gain).
Bulk + HF decoupling;
POWER RAILS (global power ports)
D1 ESD clamp: 15 kV air / 8 kV contact
USB: the S3's USB-Serial/JTAG block handles reset and
R20 holds that into U3's 40 V bus pin to 0.5 mA
Dead short: 24 V x 35 mA = 0.85 W in Q1,
IO0 (27) - internal pull-up, held high by SW2 idle.
= 0.51 W -- well inside SOT-25 on 2 oz copper.
floating is safe with no JTAG header.
LOOP CURRENT LIMITER - 35 mA, reverse blocking
D2 (SS34) and C11 are rated 40 V / 50 V for margin
+3V3 LDO -> ESP32-S3, INA226
-> 0.75 uA. Dissipation at 24 mA = 1.9 mW (0805).
Do not add a pull-up here.
Ilim = Vbe(Q2) / R16: 35 / 33 / 27 mA at
GND single ground plane
D6 at 82 mV steals 1 ppm at 25 C, 77 ppm at 85 C.
-20 / 25 / 85 C, so 24 mA always reads.

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
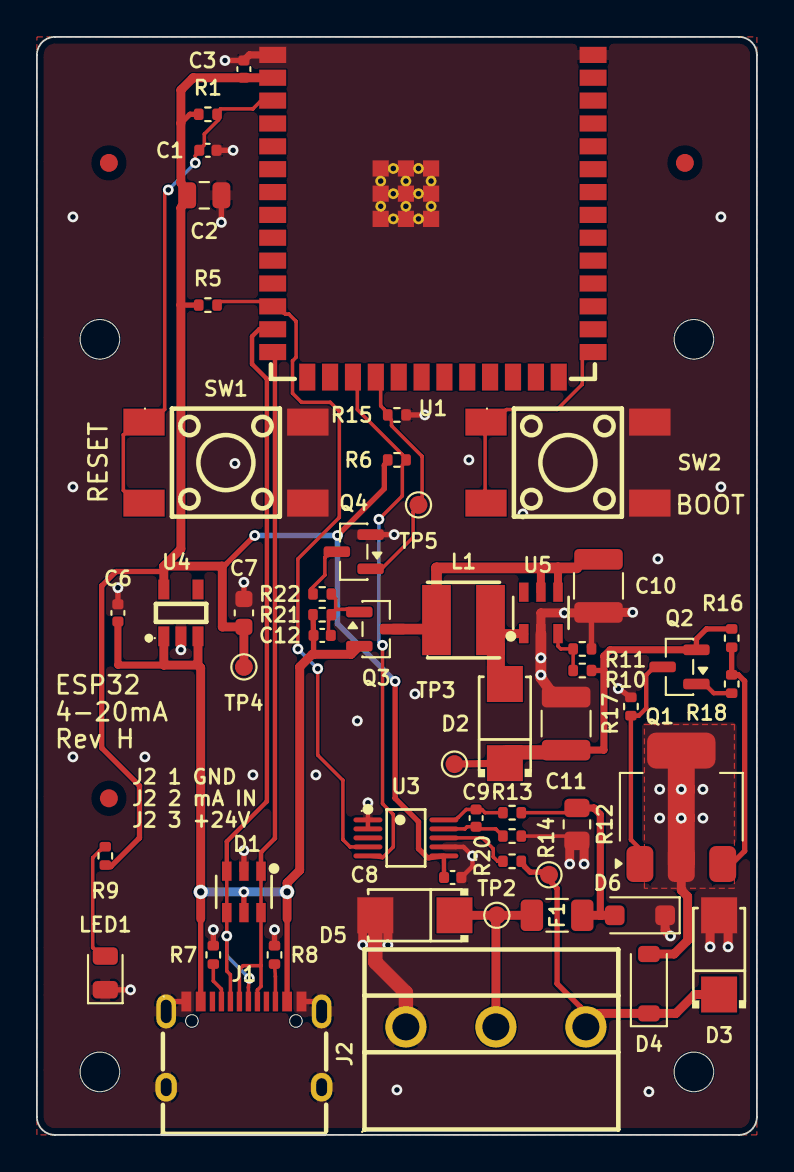
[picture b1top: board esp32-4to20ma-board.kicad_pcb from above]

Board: 2 copper layers, 40.0 x 61.0 mm, 61 parts (0 on the bottom side), 29 nets.

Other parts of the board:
FID1, FID2, FID3: Fiducial_1mm_Mask2mm
H1, H2, H3, H4: MountingHole_2.2mm

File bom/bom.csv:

Reference,Qty,Value,Footprint,MPN,Manufacturer,LCSC,LC_Stock,Chosen_Distributor,Datasheet,Validated,DNP,Notes
"C1,C6",2,1uF,0402,CL05A105KA5NQNC,Samsung Electro-Mechanics,C52923,,,https://www.lcsc.com/product-detail/C52923.html,,,
C2,1,22uF,0805,CL21A226MAQNNNE,Samsung Electro-Mechanics,C45783,,,https://www.lcsc.com/product-detail/C45783.html,,,
"C3,C8,C9,C12",4,100nF,0402,CL05B104KO5NNNC,Samsung Electro-Mechanics,C1525,,,https://www.lcsc.com/product-detail/C1525.html,,,
C7,1,10uF,0603,CL10A106KP8NNNC,Samsung Electro-Mechanics,C19702,,,https://www.lcsc.com/product-detail/C19702.html,,,
"C10,C11",2,10uF/50V,1210,CS3225X7R106K500NRL,Samwha,C2918502,,,https://www.lcsc.com/product-detail/C2918502.html,,,
D1,1,USBLC6-2SC6,SOT-23-6_L2.9-W1.6-P0.95-LS2.8-BL,USBLC6-2SC6,UMW,C2687116,,,https://www.lcsc.com/product-detail/C2687116.html,,,
D2,1,SS34,SMA_L4.3-W2.6-LS5.2-RD,SS34,MDD,C8678,,,https://www.lcsc.com/product-detail/C8678.html,,,
"D3,D5",2,SMAJ28A,SMA_L4.3-W2.6-LS5.2-RD,SMAJ28A,Jingdao Microelectronics,C353458,,,https://www.lcsc.com/product-detail/C353458.html,,,
D4,1,1N4148W,D_SOD-123,1N4148W,ST (Semtech),C81598,,,https://www.lcsc.com/product-detail/C81598.html,,,
D6,1,1N4007W,D_SOD-123F,1N4007W,MSKSEMI,C7528871,,,https://www.lcsc.com/product-detail/C7528871.html,,,
F1,1,100mA/60V,Fuse_1206_3216Metric,nSMD010,TECHFUSE,C70065,,,https://www.lcsc.com/product-detail/C70065.html,,,
J1,1,USB-C Receptacle,USB-C-SMD_TYPE-C-16PIN-2MD-073,TYPE-C 16PIN 2MD(073),SHOU HAN,C2765186,,,https://www.lcsc.com/product-detail/C2765186.html,,,
J2,1,4-20mA Loop,CONN-TH_KF250NH-5.0-3P,KF250NH-5.0-3P,Cixi Kefa,C976567,,,https://www.lcsc.com/product-detail/C976567.html,,,
L1,1,22uH,IND-SMD_L4.0-W4.0_FNR40XXS,FNR4030S220MT,cjiang,C167883,,,https://www.lcsc.com/product-detail/C167883.html,,,
LED1,1,Power,0805,NCD0805R1,Nationstar,C84256,,,https://www.lcsc.com/product-detail/C84256.html,,,
Q1,1,BCP53-16,SOT-223,BCP53-16,JSCJ,C148109,,,https://www.lcsc.com/product-detail/C148109.html,,,
Q2,1,MMBT5401,SOT-23,MMBT5401,JSCJ,C8326,,,https://www.lcsc.com/product-detail/C8326.html,,,
Q3,1,AO3401A,SOT-23,AO3401A,Alpha & Omega,C15127,,,https://www.lcsc.com/product-detail/C15127.html,,,
Q4,1,2N7002,SOT-23,2N7002,JSCJ,C8545,,,https://www.lcsc.com/product-detail/C8545.html,,,
"R1,R11,R20",3,10k,0402,0402WGF1002TCE,Uniroyal,C25744,,,https://www.lcsc.com/product-detail/C25744.html,,,
"R5,R6",2,4.7k,0402,0402WGF4701TCE,Uniroyal,C25900,,,https://www.lcsc.com/product-detail/C25900.html,,,
"R7,R8",2,5.1k,0402,0402WGF5101TCE,Uniroyal,C25905,,,https://www.lcsc.com/product-detail/C25905.html,,,
R9,1,330,0402,0402WGF3300TCE,Uniroyal,C25104,,,https://www.lcsc.com/product-detail/C25104.html,,,
"R10,R21",2,390k,0402,FRC0402F3903TS,FOJAN,C2909352,,,https://www.lcsc.com/product-detail/C2909352.html,,,was C25782 (0402WGF3903TCE) - only 14 in stock 2026-09-13
R12,1,3.32,0805,FRC0805F3R32TS,FOJAN,C3013220,,,https://www.lcsc.com/product-detail/C3013220.html,,,
"R13,R14",2,10,0402,0402WGF100JTCE,Uniroyal,C25077,,,https://www.lcsc.com/product-detail/C25077.html,,,
"R15,R22",2,100k,0402,0402WGF1003TCE,Uniroyal,C25741,,,https://www.lcsc.com/product-detail/C25741.html,,,
R16,1,18,0402,RC0402FR-0718RL,Yageo,C138043,,,https://www.lcsc.com/product-detail/C138043.html,,,
R17,1,47k,0402,0402WGF4702TCE,Uniroyal,C25792,,,https://www.lcsc.com/product-detail/C25792.html,,,
R18,1,1k,0402,0402WGF1001TCE,Uniroyal,C11702,,,https://www.lcsc.com/product-detail/C11702.html,,,
"SW1,SW2",2,RESET/BOOT,SW-SMD_4P-L6.0-W6.0-P4.50-LS9.0_H5.0,KH-6X6X5H-STM,Kinghelm,C2837531,,,https://www.lcsc.com/product-detail/C2837531.html,,,
U1,1,ESP32-S3-WROOM-1U-N4,WIFIM-SMD_ESP32-S3-WROOM-1U,ESP32-S3-WROOM-1U-N4,Espressif,C2980296,,,https://www.lcsc.com/product-detail/C2980296.html,,,
U3,1,INA226AIDGSR,MSOP-10_L3.0-W3.0-P0.50-LS5.0-BL,INA226AIDGSR,Texas Instruments,C49851,,,https://www.lcsc.com/product-detail/C49851.html,,,
U4,1,AP2112K-3.3,SOT-25-5_L2.9-W1.6-P0.95-LS2.8-BL,AP2112K-3.3TRG1,Diodes Inc,C51118,,,https://www.lcsc.com/product-detail/C51118.html,,,
U5,1,MT3608,SOT-23-6_L2.9-W1.6-P0.95-LS2.8-BL,MT3608,Aerosemi,C84817,,,https://www.lcsc.com/product-detail/C84817.html,,,

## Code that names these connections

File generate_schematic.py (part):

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    io1, io2 = s.pin("D1", "1"), s.pin("D1", "3")
    yu = io2[1] + 5.08                    # the lower run
    s.wire(dp, (DX + 30.48, dp[1]))
    s.label("USB_P", DX + 30.48, dp[1])
    s.wire(io1, (io1[0], dp[1]))
    s.wire(dn, (X + 24.13, dn[1]), (X + 24.13, yu), (DX + 25.4, yu), (DX + 25.4, dn[1]),
           (DX + 30.48, dn[1]))
    s.label("USB_N", DX + 30.48, dn[1])
    s.wire(io2, (io2[0], yu))
    dv, dg = s.pin("D1", "5"), s.pin("D1", "2")
    s.wire(dv, (dv[0] - 3.81, dv[1]), (dv[0] - 3.81, dv[1] - 5.08))
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    s.wire(s.pin("R9", "1"), (195.58, 59.69))
    s.power("+3V3", 195.58, 59.69)
    s.wire(s.pin("R9", "2"), s.pin("LED1", "2"))
    s.label("LED_A", 195.58, 74.93)
    s.wire(s.pin("LED1", "1"), (195.58, 88.9))
    s.gnd(195.58, 88.9)
    s.note("Power LED: (3.3 - 1.9) / 330 = 4.2 mA", 132.08, 93.98, 1.0)
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    put(s, "R5", 88.9, 88.9)      # SDA
    put(s, "R6", 71.12, 88.9)     # SCL
    s.wire(s.pin("U1", "12"), (81.28, 101.6))
    s.label("I2C_SDA", 81.28, 101.6, 180)
    s.wire(s.pin("R5", "2"), (88.9, 101.6))
    s.wire(s.pin("R5", "1"), (88.9, 81.28))
    s.power("+3V3", 88.9, 81.28)

    s.wire(s.pin("U1", "17"), (66.04, 114.3))
    s.label("I2C_SCL", 66.04, 114.3, 180)
    s.wire(s.pin("R6", "2"), (71.12, 114.3))
    s.wire(s.pin("R6", "1"), (71.12, 81.28))
    s.power("+3V3", 71.12, 81.28)
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    # other use here. R15 on the boost sheet holds it high, so the loop
    # supply comes up with the board and firmware can switch it off.
    s.wire(s.pin("U1", "18"), (76.2, 116.84))
    s.label("MT_EN", 76.2, 116.84, 180)

    # ---- Native USB -------------------------------------------------------
    s.wire(s.pin("U1", "13"), (82.55, 104.14))
    s.label("USB_N", 82.55, 104.14, 180)
    s.wire(s.pin("U1", "14"), (82.55, 106.68))
    s.label("USB_P", 82.55, 106.68, 180)

    # ---- Boot strap button -----------------------------------------------
    put(s, "SW2", 177.8, 116.84)
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    gx, gy = s.pin("Q3", "1")
    s.wire(s.pin("R21", "2"), (50.8, 88.9), (gx, 88.9), (gx, gy))
    s.wire(s.pin("C12", "2"), (58.42, 88.9))
    s.label("SW_GATE", 60.96, 88.9)
    s.wire((50.8, 88.9), s.pin("R22", "1"))
    s.wire(s.pin("R22", "2"), s.pin("Q4", "3"))
    s.label("SW_PD", 50.8, 101.6)
    s.wire(s.pin("Q4", "2"), (50.8, 116.84))
    s.gnd(50.8, 116.84)
    # Enable: pulled DOWN, driven high by the MCU to power the loop (Rev H).
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    # and any firmware hang, with only Q1's dissipation between a shorted loop
    # and the limit. It gates the load switch; U5's own EN rides on its input.
    s.wire(s.pin("Q4", "1"), (34.29, 109.22))
    s.label("MT_EN", 34.29, 109.22, 180)
    s.wire(s.pin("R15", "2"), (39.37, 109.22))
    s.gnd(*s.pin("R15", "1"))
    s.note("R21/R22 leave Vgs at -4.0 V; C12 x (R21 || R22) = 8 ms.", 63.5, 96.52, 1.0)
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    s.wire(s.pin("Q3", "3"), s.pin("L1", "1"))
    s.wire((83.82, Y), (83.82, Y - 5.08))
    s.power("PWR_FLAG", 83.82, Y - 5.08)
    s.label("VIN_SW", 86.36, Y)
    s.wire((101.6, Y), s.pin("C10", "1"))
    s.wire(s.pin("C10", "2"), (101.6, 90.17))
    s.gnd(101.6, 90.17)
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    s.wire(vin, (109.22, vin[1]))
    s.nc("U5", "6")
    s.wire(s.pin("L1", "2"), s.pin("D2", "2"))
    s.label("MT_SW", 139.7, Y)
    s.wire(sw, (137.16, sw[1]), (137.16, Y))
    s.wire(gnd, (gnd[0], gnd[1] + 2.54))
    s.gnd(gnd[0], gnd[1] + 2.54)
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    s.gnd(167.64, 107.95)
    # feedback: straight across from the divider's midpoint
    s.wire(fb, (167.64, fb[1]))
    s.label("MT_FB", 142.24, fb[1])
    s.wire((180.34, Y), s.pin("C11", "1"))
    s.wire(s.pin("C11", "2"), (180.34, 90.17))
    s.gnd(180.34, 90.17)
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                   ("TP4", 144.78), ("TP5", 157.48)):
        put(s, ref, x, 157.48, 180)
        s.wire(s.pin(ref, "1"), (x, 152.4))
    s.label("LOOP_V", 106.68, 152.4)
    s.label("LOOP_IN", 119.38, 152.4)
    s.power("+24V", 132.08, 152.4)
    s.power("+3V3", 144.78, 152.4)
    s.label("MT_EN", 157.48, 152.4)
    s.block_end()


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    s.power("+24V", 121.92, 134.62)
    s.wire((121.92, 134.62), (121.92, Y), s.pin("R16", "1"))
    s.wire(s.pin("R16", "2"), s.pin("Q1", "3"))
    s.label("LOOP_SNS", 140.97, Y)
    # pins 2 and 4 are both the collector (4 is the tab)
    s.wire(s.pin("Q1", "4"), s.pin("Q1", "2"))
    s.wire(s.pin("Q1", "2"), s.pin("D4", "2"))
    s.label("LOOP_C", 171.45, Y)
    s.wire(s.pin("D4", "1"), (195.58, Y))
    s.label("LOOP_V", 195.58, Y)

    # Q2 across the sense resistor: emitter on the +24 V side, base on the
    # far side through R18
    s.wire(s.pin("Q2", "2"), (124.46, Y))
    s.wire(s.pin("Q2", "1"), s.pin("R18", "2"))
    s.label("LOOP_FB", 133.35, 149.86)
    s.wire(s.pin("R18", "1"), (154.94, 149.86), (154.94, Y))

    # base drive: R17 pulls Q1's base down, Q2's collector pulls it back up
    s.wire(s.pin("Q1", "1"), (165.1, 160.02), s.pin("R17", "1"))
    s.wire(s.pin("Q2", "3"), (124.46, 160.02), (165.1, 160.02))
    s.label("LOOP_DRV", 133.35, 160.02)
    s.gnd(*s.pin("R17", "2"))

    s.note("Ilim = Vbe(Q2) / R16: 35 / 33 / 27 mA at", 175.26, 152.4, 1.0)
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    put(s, "R13", 180.34, YB, 90)        # 1 (shunt) left, 2 (IN+) right
    put(s, "R14", 180.34, 107.95, 90)    # 1 (shunt's ground end) left, 2 (IN-) right
    put(s, "C9", 189.23, 100.33)
    put(s, "R20", 177.8, YA, 90)         # 1 (LOOP_V) left, 2 (bus pin) right
    put(s, "U3", 220.98, 95.25)

    # +24 V out: terminal pin 3, its clamp, and on to the bus-voltage pin
    s.wire(p3, (111.76, p3[1]), (111.76, YA), s.pin("R20", "1"))
    s.label("LOOP_V", 127.0, YA)
    s.wire((121.92, YA), s.pin("D3", "1"))
    s.wire(s.pin("D3", "2"), (121.92, 85.09))
    s.gnd(121.92, 85.09)
    vbus = s.pin("U3", "8")
    s.wire(s.pin("R20", "2"), (vbus[0], YA), vbus)
    s.label("INA_VBUS", 184.15, YA)

    # mA in: terminal pin 2, clamp, fuse, then the shunt with its diode
    s.wire(p2, s.pin("F1", "1"))
    s.label("LOOP_IN", 124.46, YB)
    s.wire((121.92, YB), s.pin("D5", "1"))
    s.wire(s.pin("D5", "2"), (121.92, 107.95))
    s.gnd(121.92, 107.95)
    s.wire(s.pin("F1", "2"), s.pin("R13", "1"))
    s.label("LOOP_RTN", 146.05, YB)
    s.wire((160.02, YB), s.pin("D6", "2"))
    s.wire(s.pin("D6", "1"), (160.02, 107.95))
    s.gnd(160.02, 107.95)
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    # differential filter into IN+ / IN-
    inp, inn = s.pin("U3", "10"), s.pin("U3", "9")
    s.wire(s.pin("R13", "2"), inp)
    s.label("INA_INP", 191.77, YB)
    s.wire(s.pin("R14", "2"), (195.58, 107.95), (195.58, inn[1]), inn)
    s.label("INA_INN", 196.85, inn[1])
    s.wire((189.23, YB), s.pin("C9", "1"))
    s.wire(s.pin("C9", "2"), (189.23, 107.95))

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    s.nc("U3", "3")
    sda, scl = s.pin("U3", "4"), s.pin("U3", "5")
    s.wire(sda, (sda[0] + 5.08, sda[1]))
    s.label("I2C_SDA", sda[0] + 5.08, sda[1])
    s.wire(scl, (scl[0] + 5.08, scl[1]))
    s.label("I2C_SCL", scl[0] + 5.08, scl[1])

    s.note("SHUNT SIZING", 104.14, 119.38, 1.4, bold=True)
    s.note("R12 = 3.32 ohm: the INA226's +/-81.92 mV full scale", 104.14, 124.46, 1.0)
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

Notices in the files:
README.md:
Licence:
Copyright Diode663 2026.
Hardware** (the KiCad project, schematic, board, the project's own symbols and footprints,
fabrication outputs and documentation): this source describes Open Hardware and is licensed under
the CERN-OHL-P v2. You may redistribute and modify this source and make products using it under
the terms of the CERN-OHL-P v2 (), a copy of which is in
[`LICENSE`](LICENSE). This source is distributed WITHOUT ANY EXPRESS OR IMPLIED WARRANTY,
INCLUDING OF MERCHANTABILITY, SATISFACTORY QUALITY AND FITNESS FOR A PARTICULAR PURPOSE. Please
see th
